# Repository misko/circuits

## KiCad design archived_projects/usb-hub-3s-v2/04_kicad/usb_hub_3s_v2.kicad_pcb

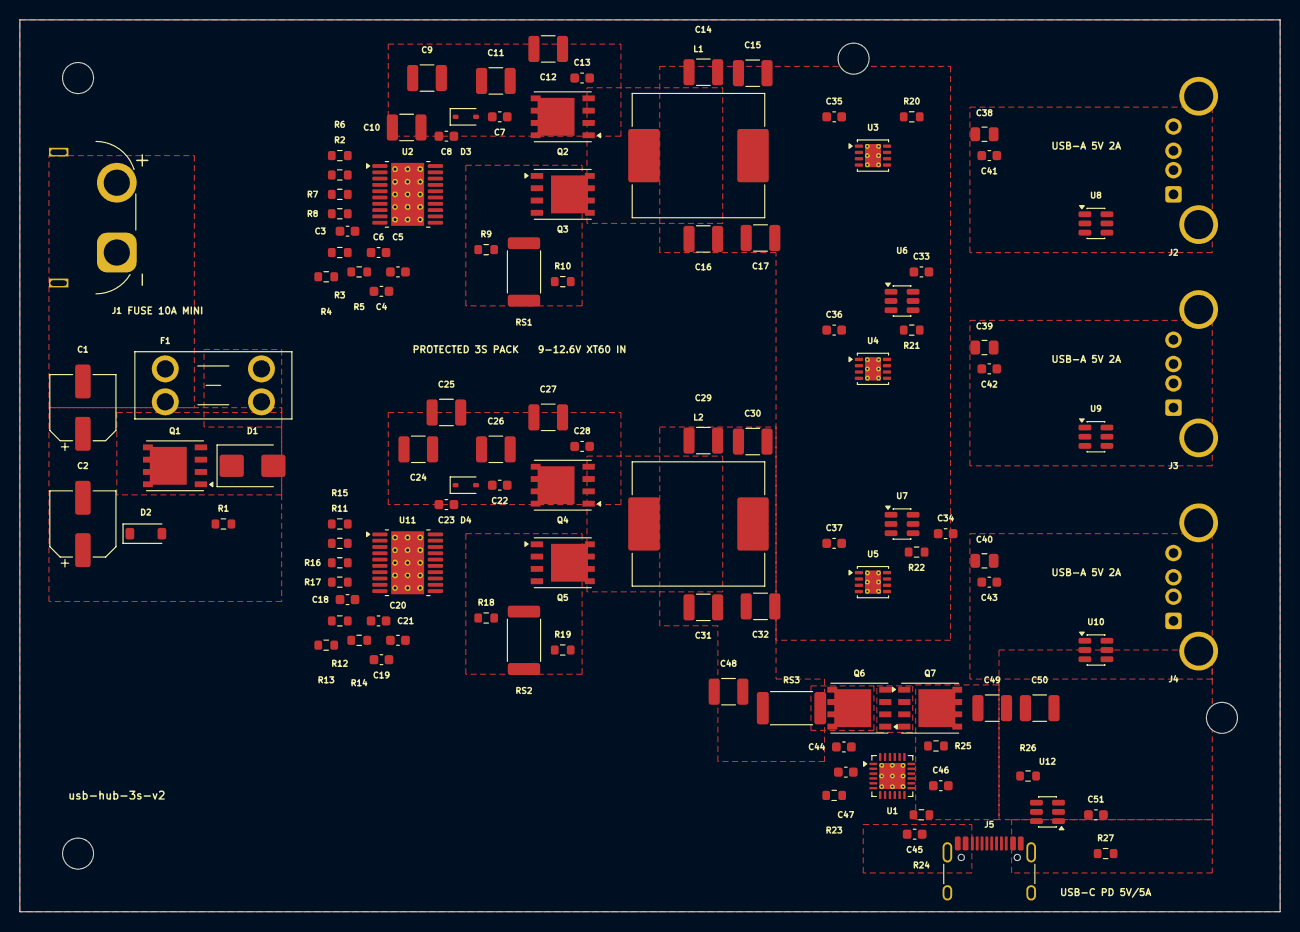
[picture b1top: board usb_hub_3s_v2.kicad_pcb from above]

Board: 4 copper layers, 130.0 x 92.0 mm, 116 parts (0 on the bottom side), 66 nets, no tracks yet.

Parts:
C1, C2: C2982822; CP_Elec_6.3x7.7
C3, C18: 330pF; C_0603_1608Metric
C4, C19: 3.3nF; C_0603_1608Metric
C5, C20: 100pF; C_0603_1608Metric
C6, C21: 10nF; C_0603_1608Metric
C7, C8, C22, C23: 1uF; C_0603_1608Metric
C9, C10, C11, C12, C24, C25, C26, C27, C48, C49, C50: 10uF; C_1210_3225Metric
C13, C28, C33, C34, C35, C36, C37, C41, C42, C43, C44, C46, C47, C51: 100nF; C_0603_1608Metric
C14, C15, C16, C17, C29, C30, C31, C32: 100uF; C_1210_3225Metric
C38, C39, C40: 22uF; C_0805_2012Metric
C45: 220nF; C_0603_1608Metric
D1: C83846; D_SMB
D2: C173429; D_SOD-123
D3, D4: C2128; D_SOD-323
F1: C5249699; Fuseholder_Blade_Mini_Keystone_3568
H1, H2, H3, H4: MountingHole_3.2mm_M3
J1: C98732; XT60PW-M_EdgeTrim
J2, J3, J4: C503996; KH-AF90DIP-112_Horizontal
J5: C5337088; TYPE-C-31-M-12_EdgeTrim
L1, L2: C408523; L_Sunlord_MWSA1206S-6R8
Q1: C2760089; PowerPAK_SO-8_Single
Q2, Q3, Q4, Q5, Q6, Q7: C404363; PowerPAK_SO-8_Single
R1, R8, R17, R23, R24: 100kΩ; R_0603_1608Metric
R2, R11: 12.4kΩ; R_0603_1608Metric
R3, R12: 3.74kΩ; R_0603_1608Metric
R4, R13: 1.21kΩ; R_0603_1608Metric
R5, R14: 18kΩ; R_0603_1608Metric
R6, R15: 49.9kΩ; R_0603_1608Metric
R7, R16: 6.98kΩ; R_0603_1608Metric
R9, R10, R18, R19, R27: 0Ω; R_0603_1608Metric
R20, R21, R22: 36.5kΩ; R_0603_1608Metric
R25: 10Ω; R_0603_1608Metric
R26: 120Ω; R_0603_1608Metric
RS1, RS2: 10mΩ; R_2512_6332Metric
RS3: 5mΩ; R_2512_6332Metric
U1: C544309; Texas_RGE0024H_VQFN-24-1EP_4x4mm_P0.5mm_EP2.7x2.7mm_Thermal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
U2, U11: C13755; HTSSOP-20-1EP_4.4x6.5mm_P0.65mm_EP3.4x6.5mm_Mask2.75x3.43mm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
U3, U4, U5: C130056; VSON-8-1EP_3x3mm_P0.65mm_EP1.65x2.4mm_ThermalVias
U6, U7: C473910; SOT-23-6
U8, U9, U10, U12: C7519; SOT-23-6

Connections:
5VA: C14.1, C15.1, C16.1, C17.1, C33.1, C34.1, C35.1, C36.1, C37.1, L1.2, R3.1, U2.10, U3.2, U3.3, U3.4, U4.2, U4.3, U4.4, U5.2, U5.3, U5.4, U6.5, U7.5
5VC: C29.1, C30.1, C31.1, C32.1, C44.1, C48.1, L2.2, R12.1, RS3.1, U1.20, U11.10
BOOT_A: C7.1, D3.1, U2.18
BOOT_C: C22.1, D4.1, U11.18
CC1: J5.A5, U1.2
CC2: J5.B5, U1.3
CMZ_A: C4.1, R5.2
CMZ_C: C19.1, R14.2
COMP_A: C5.1, R5.1, U2.9
COMP_C: C20.1, R14.1, U11.9
CSF_A: R9.2, U2.12
CSF_C: R18.2, U11.12
CSGF_A: R10.2, U2.13
CSGF_C: R19.2, U11.13
CS_A: Q3.1, Q3.2, Q3.3, R9.1, RS1.1
CS_C: Q5.1, Q5.2, Q5.3, R18.1, RS2.1
DMC: J5.A7, J5.B7, R27.2, U12.3, U12.4
DM_A1: J2.2, U6.6, U8.3, U8.4
DM_A2: J3.2, U6.4, U9.3, U9.4
DM_A3: J4.2, U7.6, U10.3, U10.4
DPC: J5.A6, J5.B6, R27.1, U12.1, U12.6
DP_A1: J2.3, U6.1, U8.1, U8.6
DP_A2: J3.3, U6.3, U9.1, U9.6
DP_A3: J4.3, U7.1, U10.1, U10.6
DSCG_N: R26.2, U1.24
DVDD: C45.1, U1.8, U1.13
EN_A: R8.2, U2.4
EN_C: R17.2, U11.4
FB_A: C4.2, C5.2, R3.2, R4.1, U2.8
FB_C: C19.2, C20.2, R12.2, R13.1, U11.8
GDNG: R25.1, U1.22
GND: C1.2, C2.2, C3.2, C6.2, C8.2, C9.2, C10.2, C11.2, C12.2, C13.2, C14.2, C15.2, C16.2, C17.2, C18.2, C21.2, C23.2, C24.2, C25.2, C26.2, C27.2, C28.2, C29.2, C30.2, C31.2, C32.2, C33.2, C34.2, C35.2, C36.2, C37.2, C38.2, C39.2, C40.2, C41.2, C42.2, C43.2, C44.2, C45.2, C46.2, C47.2, C48.2, C49.2, C50.2, C51.2, D1.2, J1.1, J2.4, J2.SH, J3.4, J3.SH, J4.4, J4.SH, J5.A1, J5.A12, J5.B1, J5.B12, J5.SH, R1.2, R2.2, R4.2, R7.2, R10.1, R11.2, R13.2, R16.2, R19.1, R20.2, R21.2, R22.2, R23.2, R24.2, RS1.2, RS2.2, U1.4, U1.9, U1.10, U1.17, U1.18, U1.25, U2.6, U2.11, U2.14, U2.17, U2.21, U3.1, U3.9, U4.1, U4.9, U5.1, U5.9, U6.2, U7.2, U8.2, U9.2, U10.2, U11.6, U11.11, U11.14, U11.17, U11.21, U12.2
HIPWR: R23.1, U1.5
HO_A: Q2.4, U2.19
HO_C: Q4.4, U11.19
ILIM1: R20.1, U3.5
ILIM2: R21.1, U4.5
ILIM3: R22.1, U5.5
LO_A: Q3.4, U2.15
LO_C: Q5.4, U11.15
PDGATE: Q6.4, Q7.4, R25.2
PDSRC: Q6.1, Q6.2, Q6.3, Q7.1, Q7.2, Q7.3, U1.23
PSEL: R24.1, U1.12
RAMP_A: C3.1, U2.5
RAMP_C: C18.1, U11.5
RPP_G: D2.2, Q1.4, R1.1
RSNS: Q6.5, RS3.2, U1.19
RT_A: R2.1, U2.3
RT_C: R11.1, U11.3
SS_A: C6.1, U2.7
SS_C: C21.1, U11.7
SW_A: C7.2, L1.1, Q2.1, Q2.2, Q2.3, Q3.5, U2.20
SW_C: C22.2, L2.1, Q4.1, Q4.2, Q4.3, Q5.5, U11.20
UVLO_A: R6.2, R7.1, U2.2
UVLO_C: R15.2, R16.1, U11.2
VAUX: C46.1, U1.14, U1.15, U1.16
VBAT: F1.1, J1.2
VBAT_F: F1.2, Q1.5
VBUSA1: C38.1, C41.1, J2.1, U3.6, U3.7, U8.5
VBUSA2: C39.1, C42.1, J3.1, U4.6, U4.7, U9.5
VBUSA3: C40.1, C43.1, J4.1, U5.6, U5.7, U10.5
VBUSC: C49.1, C50.1, C51.1, J5.A4, J5.A9, J5.B4, J5.B9, Q7.5, R26.1, U1.21, U12.5
VCC_A: C8.1, D3.2, U2.16
VCC_C: C23.1, D4.2, U11.16
VIN: C1.1, C2.1, C9.1, C10.1, C11.1, C12.1, C13.1, C24.1, C25.1, C26.1, C27.1, C28.1, D1.1, D2.1, Q1.1, Q1.2, Q1.3, Q2.5, Q4.5, R6.1, R8.1, R15.1, R17.1, U2.1, U11.1
VTX: C47.1, U1.1

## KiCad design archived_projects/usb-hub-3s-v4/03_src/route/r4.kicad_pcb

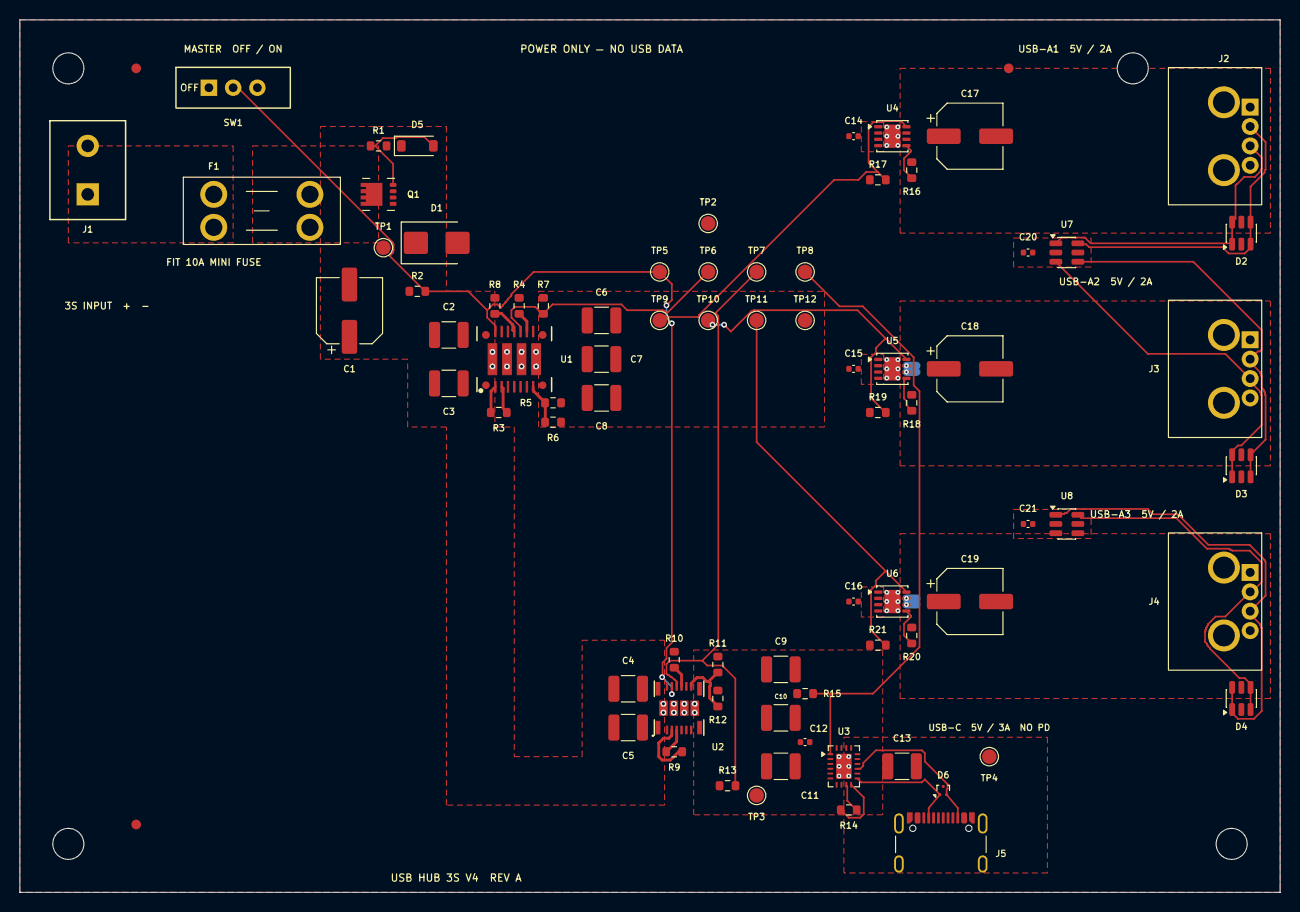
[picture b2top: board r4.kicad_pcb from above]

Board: 4 copper layers, 130.0 x 90.0 mm, 83 parts (0 on the bottom side), 40 nets.

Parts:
C1: C88744; Rubycon_TZV_D6.3x8
C2, C3, C4, C5, C13: 10uF; C_1210_3225Metric
C6, C7, C8, C9, C10, C11: 47uF; C_1210_3225Metric
C12, C14, C15, C16, C20, C21: 100nF; C_0402_1005Metric
C17, C18, C19: C264054; CP_Elec_6.3x5.8
D1: C83846; D_SMB
D2, D3, D4: C7519; SOT-23-6
D5: C124196; D_SOD-123
D6: C97502; SOT-9X3
F1: C5249699; Keystone_3568_Mini_Blade_Fuse_Holder
FID1, FID2, FID3: Fiducial_1mm_Mask2mm
H1, H2, H3, H4: MountingHole_3.2mm_M3
J1: C3817933; Phoenix_MKDS_1.5_2_1715022
J2, J3, J4: C5815149; USB_A_GCT_USB1130-15-A_Horizontal
J5: C3020560; GCT_USB4105_GF_A
Q1: C264098; Diodes_PowerDI3333-8_Type_UX
R1, R2: 1MΩ; R_0603_1608Metric
R3, R9: 0Ω; R_0603_1608Metric
R4: 15.8kΩ; R_0603_1608Metric
R5: 41.2kΩ; R_0603_1608Metric
R6, R12: 10kΩ; R_0603_1608Metric
R7, R13, R14, R15, R17, R19, R21: 100kΩ; R_0603_1608Metric
R8: 20kΩ; R_0603_1608Metric
R10: 13kΩ; R_0603_1608Metric
R11: 41.7kΩ; R_0603_1608Metric
R16, R18, R20: 39.2kΩ; R_0603_1608Metric
SW1: C273394; E_Switch_EG1218
TP1, TP2, TP3, TP4, TP5, TP6, TP7, TP8, TP9, TP10, TP11, TP12: TP; TestPoint_Pad_D1.5mm
U1: C7125816; Texas_RDF0022A_B3QFN-22_6.5x7.5mm_ThermalVias
U2: C5219289; Texas_RDL0020A_B3QFN-20_5x5.5mm_ThermalVias
U3: C473913; Texas_RVC0020A_WQFN-20-1EP_3x4mm_P0.5mm_EP1.6x2.6mm_Thermal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
U4, U5, U6: C130056; VSON-8-1EP_3x3mm_P0.65mm_EP1.65x2.4mm_ThermalVias
U7, U8: C473910; SOT-23-6

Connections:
5VA: C6.1, C7.1, C8.1, C14.1, C15.1, C16.1, C20.1, C21.1, R5.1, R7.1, R17.1, R19.1, R21.1, TP2.1, U1.5, U1.9, U1.10, U4.2, U4.3, U4.4, U5.2, U5.3, U5.4, U6.2, U6.3, U6.4, U7.5, U8.5
5VC_RAW: C9.1, C10.1, C11.1, C12.1, R11.1, R13.1, R15.1, TP3.1, U2.5, U2.8, U2.9, U3.2, U3.3, U3.4, U3.5, U3.6, U3.7, U3.8
BAT_POS: F1.1, J1.1
BOOT_A_C: R3.2, U1.3
BOOT_A_R: R3.1, U1.2
BOOT_C_C: R9.2, U2.3
BOOT_C_R: R9.1, U2.4
CC1: D6.1, J5.A5, U3.11
CC2: D6.2, J5.B5, U3.13
DM_A1: D2.3, D2.4, J2.2, U7.6
DM_A2: D3.3, D3.4, J3.2, U7.4
DM_A3: D4.3, D4.4, J4.2, U8.6
DP_A1: D2.1, D2.6, J2.3, U7.1
DP_A2: D3.1, D3.6, J3.3, U7.3
DP_A3: D4.1, D4.6, J4.3, U8.1
EN_BUS: R2.2, SW1.2, TP5.1, U1.17, U2.14
FAULT_A1: R17.2, TP9.1, U4.8
FAULT_A2: R19.2, TP10.1, U5.8
FAULT_A3: R21.2, TP11.1, U6.8
FAULT_C: R15.2, TP8.1, U3.1
FB_A: R5.2, R6.1, U1.8
FB_C: R11.2, R12.1, U2.10
GND: C1.2, C2.2, C3.2, C4.2, C5.2, C6.2, C7.2, C8.2, C9.2, C10.2, C11.2, C12.2, C13.2, C14.2, C15.2, C16.2, C17.2, C18.2, C19.2, C20.2, C21.2, D1.2, D2.2, D3.2, D4.2, D6.3, J1.2, J2.4, J2.SH, J3.4, J3.SH, J4.4, J4.SH, J5.A1, J5.A12, J5.B1, J5.B12, J5.SH, R1.2, R4.2, R6.2, R8.2, R10.2, R12.2, R16.2, R18.2, R20.2, SW1.1, TP12.1, U1.7, U1.11, U1.15, U1.19, U1.20, U1.21, U1.22, U2.6, U2.11, U2.17, U2.18, U2.19, U2.20, U3.12, U3.21, U4.1, U4.9, U5.1, U5.9, U6.1, U6.9, U7.2, U8.2
ILIM_A1: R16.1, U4.5
ILIM_A2: R18.1, U5.5
ILIM_A3: R20.1, U6.5
PG_A: R7.2, TP6.1, U1.13
PG_C: R13.2, TP7.1, U2.13
REF_C: R14.1, U3.10
REF_RTN_C: R14.2, U3.9
RPP_GATE: D5.2, Q1.4, R1.1
RT_A: R4.1, U1.12
RT_C: R10.1, U2.12
SPSP_A: R8.1, U1.14
VBAT_FUSED: F1.2, Q1.5, Q1.6, Q1.7, Q1.8
VBUSA1: C17.1, D2.5, J2.1, U4.6, U4.7
VBUSA2: C18.1, D3.5, J3.1, U5.6, U5.7
VBUSA3: C19.1, D4.5, J4.1, U6.6, U6.7
VBUSC: C13.1, J5.A4, J5.A9, J5.B4, J5.B9, TP4.1, U3.14, U3.15
VIN: C1.1, C2.1, C3.1, C4.1, C5.1, D1.1, D5.1, Q1.1, Q1.2, Q1.3, R2.1, TP1.1, U1.1, U1.18, U2.1, U2.16

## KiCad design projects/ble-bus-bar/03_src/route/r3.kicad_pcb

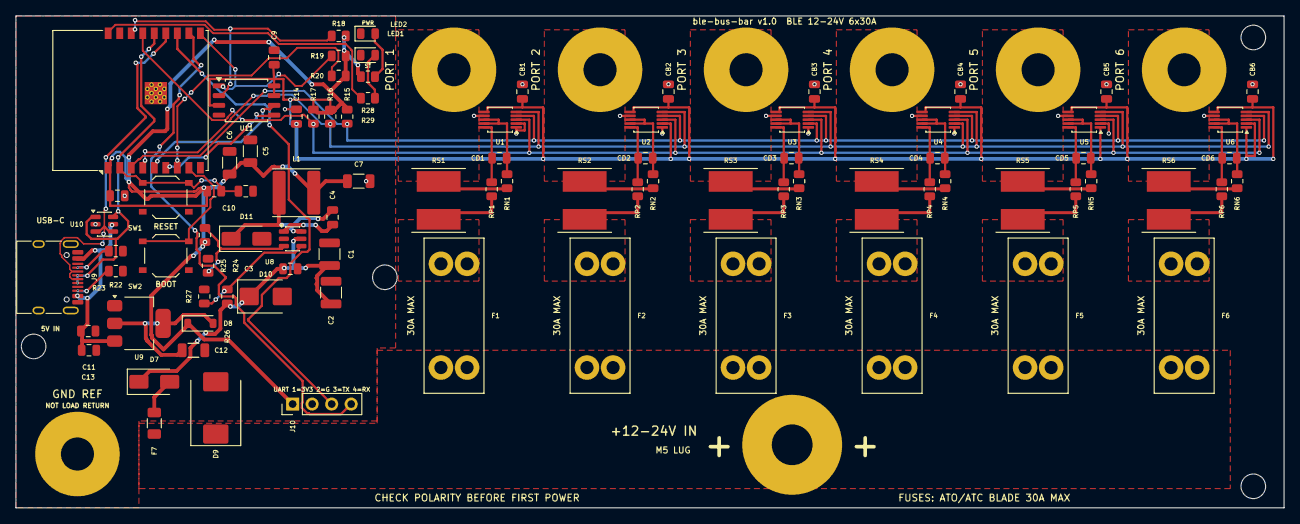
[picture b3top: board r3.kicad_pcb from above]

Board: 2 copper layers, 165.0 x 64.0 mm, 101 parts (0 on the bottom side), 55 nets.

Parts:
C1, C2: 4u7 50V; C_1210_3225Metric
C3: 100n VIN; C_0805_2012Metric
C4: 100n boot; C_0805_2012Metric
C5, C6: 22u 3V3; C_1206_3216Metric
C7: 22u U7; C_1206_3216Metric
C8: 100n U7; C_0805_2012Metric
C9: 100n U11; C_0805_2012Metric
C10: 1u EN; C_0805_2012Metric
C11: 10u LDO in; C_0805_2012Metric
C12: 22u LDO out; C_1206_3216Metric
C13: 100n VUSB; C_0805_2012Metric
C14: 100n corridor 3V3; C_0805_2012Metric
CB1, CB2, CB3, CB4, CB5, CB6: 100n INA; C_0805_2012Metric
CD1, CD2, CD3, CD4, CD5, CD6: 100n diff; C_0805_2012Metric
D7: SS310 rev block; D_SMA
D8: B5819W OR; D_SOD-123
D9: SMCJ33A bus TVS; D_SMC
D10: SMBJ33A tap TVS; D_SMB
D11: SS310 catch; D_SMA
F1, F2, F3, F4, F5, F6: 3557-2 ATO 30A MAX; FuseHolder_Keystone_3557-2
F7: 0466002 2A; Fuse_1206_3216Metric
H1, H2, H3, H4: MountingHole_3.2mm_M3
J1: PORT 1 M4 LUG; Lug_M4
J2: PORT 2 M4 LUG; Lug_M4
J3: PORT 3 M4 LUG; Lug_M4
J4: PORT 4 M4 LUG; Lug_M4
J5: PORT 5 M4 LUG; Lug_M4
J6: PORT 6 M4 LUG; Lug_M4
J7: +12-24V IN M5 LUG; Lug_M5
J8: GND REF M4 LUG; Lug_M4
J9: TYPE-C-31-M-12; USB_C_Receptacle_HRO_TYPE-C-31-M-12
J10: DEBUG UART DNP; PinHeader_1x04_P2.54mm_Vertical
L1: 22u SWPA6045S; L_Sunlord_SWPA6045S
LED1: KT-0805G PWR; LED_0805_2012Metric
LED2: KT-0805G ST; LED_0805_2012Metric
R15: 4k7 SDA pu; R_0805_2012Metric
R16: 4k7 SCL pu; R_0805_2012Metric
R17: 10k ALERT pu; R_0805_2012Metric
R18: 10k IO2 pu; R_0805_2012Metric
R19: 10k CS pu; R_0805_2012Metric
R20: 10k IO8 pu; R_0805_2012Metric
R21: 10k EN pu; R_0805_2012Metric
R22: 5k1 CC1; R_0805_2012Metric
R23: 5k1 CC2; R_0805_2012Metric
R24: 33k FB hi; R_0805_2012Metric
R25: 10k FB lo; R_0805_2012Metric
R26: 560k UVLO hi; R_0805_2012Metric
R27: 100k UVLO lo; R_0805_2012Metric
R28: 2k PWR LED; R_0805_2012Metric
R29: 1k ST LED; R_0805_2012Metric
RN1, RN2, RN3, RN4, RN5, RN6: 10R sense-; R_0805_2012Metric
RP1, RP2, RP3, RP4, RP5, RP6: 10R sense+; R_0805_2012Metric
RS1, RS2, RS3, RS4, RS5, RS6: WSLP2726 0.5mR; R_Shunt_WSLP2726
SW1: RESET; SW_Push_1P1T_XKB_TS-1187A
SW2: BOOT; SW_Push_1P1T_XKB_TS-1187A
U1, U2, U3, U4, U5, U6: INA238AIDGSR; MSOP-10_3x3mm_P0.5mm
U7: ESP32-C3-WROOM-02-N4; ESP32-C3-WROOM-02_D03
U8: LMR16006XDDCR; TSOT-23-6
U9: AMS1117-3.3; SOT-223-3_TabPin2
U10: USBLC6-2SC6; SOT-23-6
U11: W25Q64JVSSIQ; SOIC-8_5.3x5.3mm_P1.27mm

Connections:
3V3: C8.1, C9.1, CB1.1, CB2.1, CB3.1, CB4.1, CB5.1, CB6.1, U1.6, U2.2, U2.6, U3.6, U4.6, U5.1, U5.6, U6.1, U6.2, U6.6, U11.3, U11.7, U11.8
ALERT: R17.1, U1.3, U2.3, U3.3, U4.3, U5.3, U6.3, U7.15
BOOT: C4.1, U8.1
BOOT9: SW2.1, U7.8
CC1: J9.A5, R22.1
CC2: J9.B5, R23.1
EN: C10.1, R21.2, SW1.1, U7.2
FB: R24.2, R25.1, U8.3
FLASH_CS: R19.1, U7.10, U11.1
GND: C1.2, C2.2, C3.2, C5.2, C6.2, C7.2, C8.2, C9.2, C10.2, C11.2, C12.2, C13.2, C14.2, CB1.2, CB2.2, CB3.2, CB4.2, CB5.2, CB6.2, D9.2, D10.2, D11.2, J8.1, J9.A1, J9.A12, J9.B1, J9.B12, J9.SH, J10.2, LED1.1, LED2.1, R22.2, R23.2, R25.2, R27.2, SW1.2, SW2.2, U1.1, U1.2, U1.7, U2.1, U2.7, U3.1, U3.7, U4.1, U4.7, U5.2, U5.7, U6.7, U7.9, U7.19, U8.2, U9.1, U10.2, U11.4
IO8: R20.1, U7.7
KA1: CD1.1, RP1.2, U1.10
KA2: CD2.1, RP2.2, U2.10
KA3: CD3.1, RP3.2, U3.10
KA4: CD4.1, RP4.2, U4.10
KA5: CD5.1, RP5.2, U5.10
KA6: CD6.1, RP6.2, U6.10
KB1: CD1.2, RN1.2, U1.8, U1.9
KB2: CD2.2, RN2.2, U2.8, U2.9
KB3: CD3.2, RN3.2, U3.8, U3.9
KB4: CD4.2, RN4.2, U4.8, U4.9
KB5: CD5.2, RN5.2, U5.8, U5.9
KB6: CD6.2, RN6.2, U6.8, U6.9
LED1A: LED1.2, R28.2
LED2A: LED2.2, R29.2
LED_ST: R29.1, U7.18
RXD: J10.4, U7.11
SCL: R16.1, U1.5, U2.5, U3.5, U4.2, U4.5, U5.5, U6.5, U7.4
SDA: R15.1, U1.4, U2.4, U3.2, U3.4, U4.4, U5.4, U6.4, U7.3
SHDN: R26.2, R27.1, U8.4
SPI_CLK: U7.5, U11.6
SPI_MISO: R18.1, U7.16, U11.2
SPI_MOSI: U7.6, U11.5
SW: C4.2, D11.1, L1.1, U8.6
TMP_3V3: C5.1, C6.1, C7.1, C14.1, D8.1, J10.1, L1.2, R15.2, R16.2, R17.2, R18.2, R19.2, R20.2, R21.1, R24.1, R28.1, U7.1
TXD: J10.3, U7.12
USB_DM: J9.A7, J9.B7, U7.13, U10.3, U10.4
USB_DP: J9.A6, J9.B6, U7.14, U10.1, U10.6
VBUS: D9.1, F1.1, F2.1, F3.1, F4.1, F5.1, F6.1, F7.1, J7.1
VF1: F1.2, RP1.1, RS1.1
VF2: F2.2, RP2.1, RS2.1
VF3: F3.2, RP3.1, RS3.1
VF4: F4.2, RP4.1, RS4.1
VF5: F5.2, RP5.1, RS5.1
VF6: F6.2, RP6.1, RS6.1
VIN_E: C1.1, C2.1, C3.1, D7.1, D10.1, R26.1, U8.5
VLDO: C12.1, D8.2, U9.2
VP1: J1.1, RN1.1, RS1.2
VP2: J2.1, RN2.1, RS2.2
VP3: J3.1, RN3.1, RS3.2
VP4: J4.1, RN4.1, RS4.2
VP5: J5.1, RN5.1, RS5.2
VP6: J6.1, RN6.1, RS6.2
VTAP: D7.2, F7.2
VUSB: C11.1, C13.1, J9.A4, J9.A9, J9.B4, J9.B9, U9.3, U10.5
